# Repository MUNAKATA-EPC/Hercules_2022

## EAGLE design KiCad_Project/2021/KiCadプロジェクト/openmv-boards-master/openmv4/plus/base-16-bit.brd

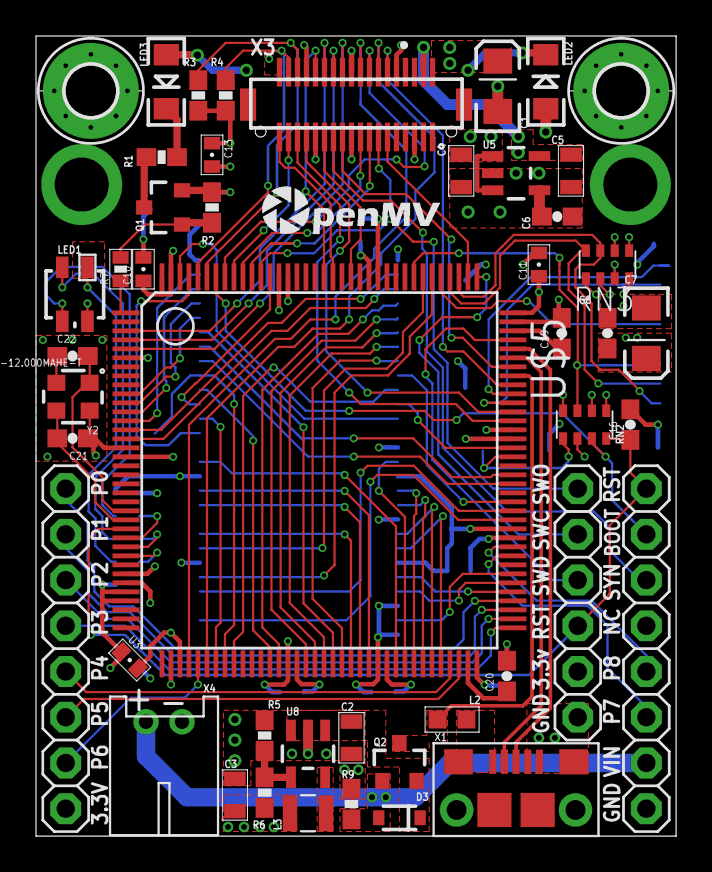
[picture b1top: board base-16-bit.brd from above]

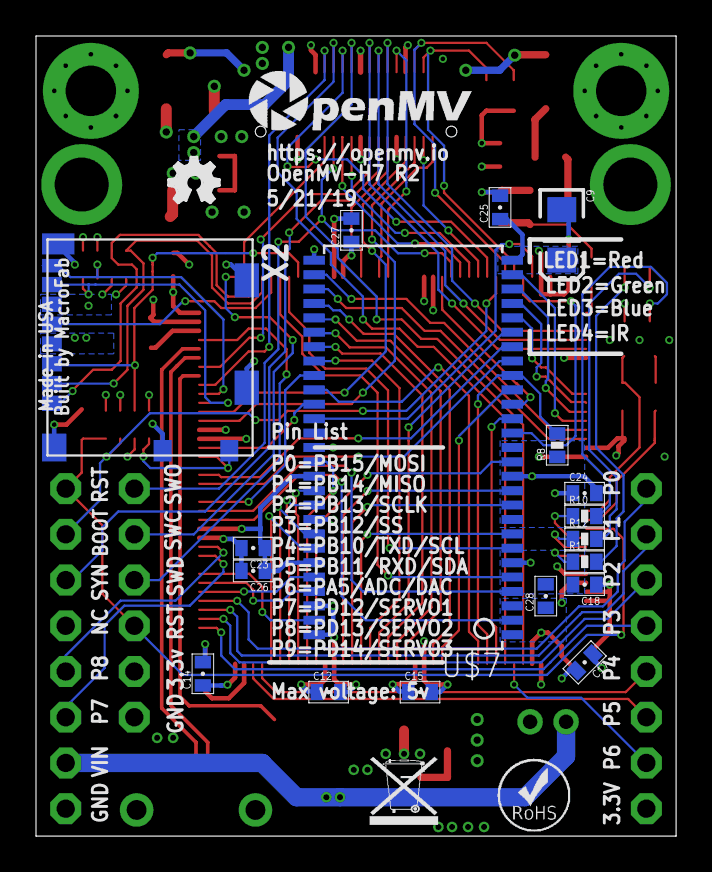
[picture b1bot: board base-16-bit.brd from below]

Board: 4 copper layers, 35.6 x 44.5 mm, 72 parts (22 on the bottom side), 108 nets.

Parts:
C1, C7: 47uF; EIA3216
C2, C3: 22uF; 0805
C4, C5: 10uF; 0805
C6, C8: 0.1uF; 0603-CAP
C9: 100uF; EIA3216
C10, C11, C12, C13, C14, C15, C18, C23, C24, C25, C26, C27, C28: 0.1uF; 0402-CAP
C16: 1uF; 0603-CAP
C17: 1uF; 0402-CAP
C19, C20: 2.2uF; 0603-CAP
C21, C22: 12pF; 0603-CAP
D3: SDM2U20SD3-7; SOD-323
H1, H2: MOUNT-PAD-ROUND2.8; 2,8-PAD
JP1, JP2: 1X08
JP3: 1X06
L2: MPZ1608S181ATAH0; 0603
L3: 4.7uH/1.4A; 1007
LED1: LED-TRICOLOR; LED-TRICOLOR-SMD
LED2, LED3: VSMY12850; LED-1206
LOGO1: OSHW_LOGO_FILLX0100-NT; OSHW_FILLX100_NOTEXT
M1, M2: 9774030243R; 9774030151R
Q1: BSS138; SOT23-3
Q2: Si2301BDS; SOT23-3
R1: 10R; 0603-RES
R2, R9: 10K; 0603-RES
R3, R4: 4.7K; 0603-RES
R5: 100K; 0603-RES
R6: 453K; 0603-RES
R7, R10, R11, R12: 220R; 0402-RES
R8: 10K; 0402-RES
RN2: 10K; EXBV8V
RN3: 220R; EXBV8V
U3: BEAD; 0402-CAP
U5: TPS731XX; SOT23-5
U8: PAM2305AABADJ; TSOT25
U$1: WEEE
U$2: ROHS
U$3: OMV-LOGO
U$4: OMV-LOGO-SMALL
U$5: STM32H743ZIT6; LQFP144@1
U$7: IS42S16160G; TSOPII-54
X1: MF-CON-MICROUSB-RIGHT; MICROUSB-RIGHT
X2: USD-1040310811; 1040310811
X3: DF12-36-DS
X4: S2B-PH-K-S(LF)(SN); JST-PH-2-THM-RA
Y2: 7S-12.000MAHE-T; CRYSTAL-2.5X2.0

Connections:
BOOT0: JP2.2, RN2.3, U$5.138
DAC: JP1.7, U$5.41
DCMI_CLK: U$5.100, X3.12
DCMI_D0: U$5.96, X3.31
DCMI_D1: U$5.97, X3.29
DCMI_D2: U$5.125, X3.35
DCMI_D3: U$5.126, X3.28
DCMI_D4: U$5.3, X3.26
DCMI_D5: U$5.136, X3.33
DCMI_D6: U$5.4, X3.24
DCMI_D7: U$5.5, X3.22
DCMI_FSIN: JP2.3, X3.23
DCMI_HSYNC: U$5.40, X3.18
DCMI_PCLK: U$5.42, X3.14
DCMI_PWDN: U$5.123, X3.25
DCMI_RST: U$5.102, X3.21
DCMI_VSYNC: U$5.137, X3.16
DRAM_A0: U$5.10, U$7.23
DRAM_A1: U$5.11, U$7.24
DRAM_A2: U$5.12, U$7.25
DRAM_A3: U$5.13, U$7.26
DRAM_A4: U$5.14, U$7.29
DRAM_A5: U$5.15, U$7.30
DRAM_A6: U$5.50, U$7.31
DRAM_A7: U$5.53, U$7.32
DRAM_A8: U$5.54, U$7.33
DRAM_A9: U$5.55, U$7.34
DRAM_A10: U$5.56, U$7.22
DRAM_A11: U$5.57, U$7.35
DRAM_A12: U$5.87, U$7.36
DRAM_BA0: U$5.89, U$7.20
DRAM_BA1: U$5.90, U$7.21
DRAM_CAS: U$5.132, U$7.17
DRAM_CLK: U$5.93, U$7.38
DRAM_CLKE: U$5.45, U$7.37
DRAM_CS: R8.2, U$5.44, U$7.19
DRAM_D0: U$5.85, U$7.2
DRAM_D1: U$5.86, U$7.4
DRAM_D2: U$5.114, U$7.5
DRAM_D3: U$5.115, U$7.7
DRAM_D4: U$5.58, U$7.8
DRAM_D5: U$5.59, U$7.10
DRAM_D6: U$5.60, U$7.11
DRAM_D7: U$5.63, U$7.13
DRAM_D8: U$5.64, U$7.42
DRAM_D9: U$5.65, U$7.44
DRAM_D10: U$5.66, U$7.45
DRAM_D11: U$5.67, U$7.47
DRAM_D12: U$5.68, U$7.48
DRAM_D13: U$5.77, U$7.50
DRAM_D14: U$5.78, U$7.51
DRAM_D15: U$5.79, U$7.53
DRAM_DQMH: U$5.142, U$7.39
DRAM_DQML: U$5.141, U$7.15
DRAM_RAS: U$5.49, U$7.18
DRAM_WE: U$5.43, U$7.16
FS_DM: U$5.103, X1.2
FS_DP: U$5.104, X1.3
GND: C1.C, C2.1, C3.1, C4.1, C5.1, C6.2, C7.C, C8.2, C9.C, C10.2, C11.2, C12.2, C13.2, C14.2, C15.2, C16.2, C17.2, C18.2, C19.2, C20.2, C21.1, C22.1, C23.2, C24.2, C25.2, C26.2, C27.2, C28.2, JP2.8, JP3.6, Q1.2, R2.1, R5.1, R9.1, RN2.6, U5.2, U8.2, U$5.16, U$5.31, U$5.38, U$5.51, U$5.61, U$5.83, U$5.94, U$5.107, U$5.120, U$5.130, U$7.6, U$7.12, U$7.28, U$7.41, U$7.46, U$7.52, U$7.54, X1.5, X2.CD$2, X2.G$1, X2.G$2, X2.G$3, X2.G$4, X2.P$6, X3.5, X3.19, X3.27, X4.2, Y2.2, Y2.4
I2C1_SCL: R3.2, U$5.139, X3.32
I2C1_SDA: R4.2, U$5.140, X3.34
I2C2_SCL: JP1.5, U$5.69
I2C2_SDA: JP1.6, U$5.70
LED_B: R11.1, U$5.28
LED_G: R12.1, U$5.27
LED_IR: R7.1, U$5.1
LED_R: R10.1, U$5.26
unnamed: Q1.1, R2.2, R7.2
unnamed: LED1.B, R11.2
unnamed: L2.1, X1.1
unnamed: LED1.R, R10.2
unnamed: LED1.G, R12.2
unnamed: LED3.C, R1.2
unnamed: C6.1, U5.4
unnamed: R5.2, R6.1, U8.4
unnamed: Q1.3, R1.1
unnamed: LED2.C, LED3.A
unnamed: C21.2, U$5.24, Y2.3
unnamed: C22.2, U$5.23, Y2.1
unnamed: C17.1, C18.1, U3.1, U$5.32, U$5.33
NRST: C16.1, JP2.1, JP3.4, RN2.4, U$5.25
RAW: C2.2, D3.1, Q2.2, U8.1, U8.3
SDIO_CLK: U$5.113, X2.P$5
SDIO_CMD: RN2.7, U$5.116, X2.P$3
SDIO_D0: RN3.8, U$5.98, X2.P$7
SDIO_D1: RN3.7, U$5.99, X2.P$8
SDIO_D2: RN3.3, U$5.111, X2.P$1
SDIO_D3: RN3.4, U$5.112, X2.P$2
SD_CD: RN2.1, U$5.92, X2.CD$1
SPI2_MISO: JP1.2, U$5.75
SPI2_MOSI: JP1.1, U$5.76
SPI2_NSS: JP1.4, U$5.73
SPI2_SCLK: JP1.3, U$5.74
SPI3_MISO: U$5.134, X3.15
SPI3_MOSI: U$5.135, X3.17
SPI3_SCLK/TRACESWO: JP3.1, U$5.133, X3.13
SPI3_SSEL: U$5.110, X3.11
SW: L3.1, U8.5
SWCLK: JP3.2, U$5.109
SWDIO: JP3.3, U$5.105
TIM4_CH1: JP2.6, U$5.81
TIM4_CH2: JP2.5, U$5.82
VBUS: L2.2, Q2.3, U$5.101
VCAP1: C19.1, U$5.106
VCAP2: C20.1, U$5.71
VCC: C1.A, C3.2, C4.2, C7.A, C8.1, C9.A, C10.1, C11.1, C12.1, C13.1, C14.1, C15.1, C23.1, C24.1, C25.1, C26.1, C27.1, C28.1, JP1.8, JP3.5, L3.2, LED1.A, LED2.A, R3.1, R4.1, R6.2, R8.1, RN2.2, RN2.5, RN2.8, RN3.1, RN3.2, RN3.5, RN3.6, U3.2, U5.1, U5.3, U$5.6, U$5.17, U$5.30, U$5.39, U$5.52, U$5.62, U$5.72, U$5.84, U$5.95, U$5.108, U$5.121, U$5.131, U$5.143, U$5.144, U$7.1, U$7.3, U$7.9, U$7.14, U$7.27, U$7.43, U$7.49, X2.P$4, X3.2, X3.10, X3.20, X3.30, X3.36
VDDA: C5.2, U5.5, X3.4
VIN: D3.2, JP2.7, Q2.1, R9.2, X4.1

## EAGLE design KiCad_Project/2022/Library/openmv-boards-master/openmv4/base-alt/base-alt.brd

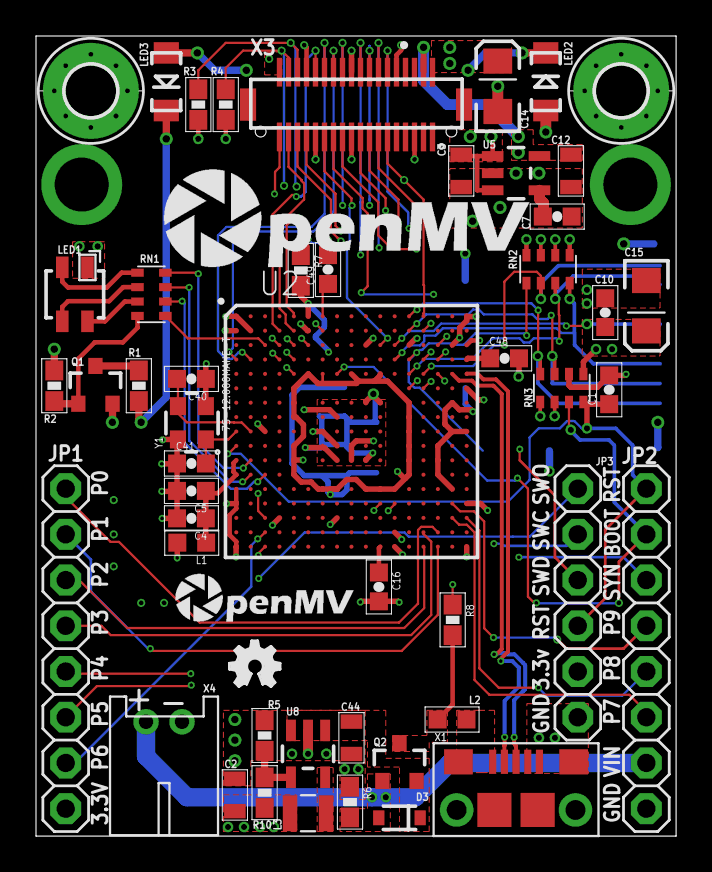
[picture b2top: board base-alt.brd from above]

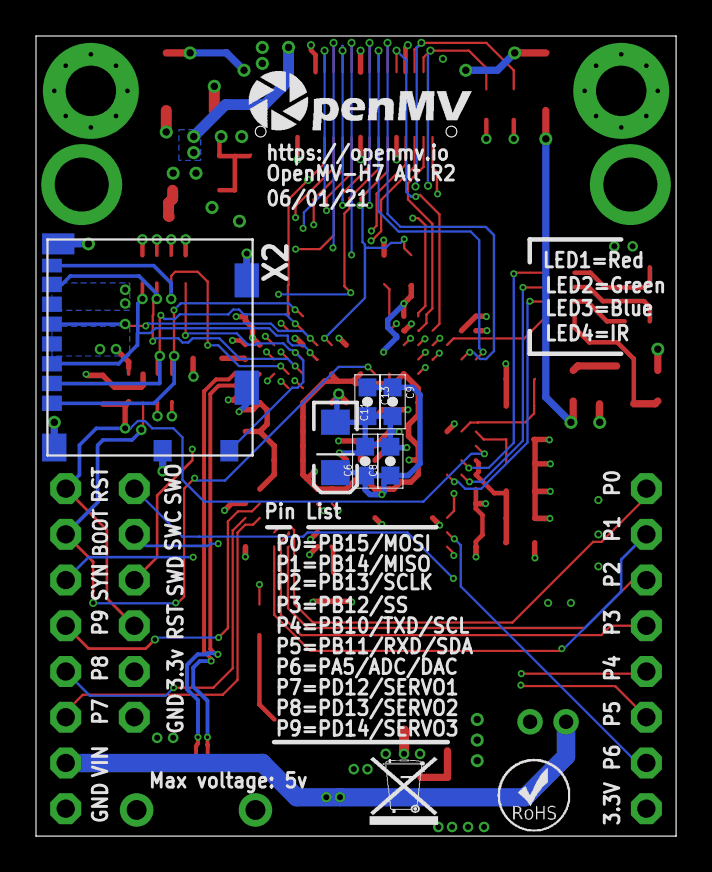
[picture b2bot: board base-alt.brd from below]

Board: 4 copper layers, 35.6 x 44.5 mm, 63 parts (9 on the bottom side), 72 nets.

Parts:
C1, C4: 1uF; 0603-CAP
C2, C44: 22uF; 0805
C3, C12: 10uF; 0805
C5, C6, C7, C8, C9, C10, C13: 0.1uF; 0603-CAP
C11, C14, C15: 47uF; EIA3216
C16, C48, C49: 2.2uF; 0603-CAP
C40, C41: 12pF; 0603-CAP
D3: SDM2U20SD3-7; SOD-323
H1, H2: MOUNT-PAD-ROUND2.8; 2,8-PAD
JP1, JP2: 1X08
JP3: 1X06
L1, L2: MPZ1608S181ATAH0; 0603
L3: 4.7uH/1.4A; 1007
LED1: LED-TRICOLOR; LED-TRICOLOR-SMD-MF
LED2, LED3: VSMY12850; LED-1206
LOGO1: OSHW_LOGO_FILLX0100-NT; OSHW_FILLX100_NOTEXT
M1, M2: 9774030243R; 9774030151R
Q1: BSS138; SOT23-3
Q2: Si2301BDS; SOT23-3
R1: 10R; 0603-RES
R2, R7: 10K; 0603-RES
R3, R4: 4.7K; 0603-RES
R5, R6: 100K; 0603-RES
R8: 560R; 0603-RES
R10: 453K; 0603-RES
RN1: 220R; EXBV8V
RN2, RN3: 10K; EXBV8V
U2: STM32H743XIH6; TFBGA240+25
U5: TPS731XX; SOT23-5
U8: PAM2305AABADJ; TSOT25
U$1: WEEE
U$2: ROHS
U$3: OMV-LOGO
U$4: OMV-LOGO-SMALL
U$6: OMV-LOGO-BIG
X1: MF-CON-MICROUSB-RIGHT; MICROUSB-RIGHT
X2: USD-1040310811; 1040310811
X3: DF12-36-DS
X4: S2B-PH-K-S(LF)(SN); JST-PH-2-THM-RA
Y1: 7S-12.000MAHE-T; CRYSTAL-2.5X2.0

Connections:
BOOT0: JP2.2, RN3.3, U2.E8
DAC: JP1.7, U2.T3
DCMI_CLK: U2.E15, X3.12
DCMI_D0: U2.F14, X3.31
DCMI_D1: U2.F13, X3.29
DCMI_D2: U2.C4, X3.35
DCMI_D3: U2.B4, X3.28
DCMI_D4: U2.D2, X3.26
DCMI_D5: U2.B5, X3.33
DCMI_D6: U2.D1, X3.24
DCMI_D7: U2.E5, X3.22
DCMI_FSIN: JP2.3, X3.23
DCMI_HSYNC: U2.U3, X3.18
DCMI_PCLK: U2.R3, X3.14
DCMI_PWDN: R7.1, U2.C11, X3.25
DCMI_RST: U2.D14, X3.21
DCMI_VSYNC: U2.C5, X3.16
FS_D_N: U2.E17, X1.2
FS_D_P: U2.E16, X1.3
GND: C1.2, C2.1, C3.1, C4.2, C5.2, C6.2, C7.2, C8.2, C9.2, C10.2, C11.C, C12.1, C13.2, C14.C, C15.C, C16.2, C40.1, C41.1, C44.1, C48.2, C49.2, JP2.8, JP3.6, Q1.2, R2.1, R5.1, R6.1, RN3.6, U2.A1, U2.A17, U2.B2, U2.B6, U2.C10, U2.C13, U2.C16, U2.G7, U2.G8, U2.G9, U2.G10, U2.G11, U2.G16, U2.H7, U2.H8, U2.H9, U2.H10, U2.H11, U2.J3, U2.J7, U2.J8, U2.J9, U2.J10, U2.J11, U2.J16, U2.J17, U2.K7, U2.K8, U2.K9, U2.K10, U2.K11, U2.K15, U2.L7, U2.L8, U2.L9, U2.L10, U2.L11, U2.L15, U2.M15, U2.N1, U2.N16, U2.P1, U2.R4, U2.R8, U2.T12, U2.U1, U2.U17, U5.2, U8.2, X1.5, X2.CD$2, X2.G$1, X2.G$2, X2.G$3, X2.G$4, X2.P$6, X3.5, X3.19, X3.27, X4.2, Y1.2, Y1.4
I2C1_SCL: R3.2, U2.D5, X3.32
I2C1_SDA: R4.2, U2.D4, X3.34
I2C2_SCL: JP1.5, U2.P11
I2C2_SDA: JP1.6, U2.P12
LED_B: RN1.6, U2.M3
LED_G: RN1.7, U2.M2
LED_IR: RN1.5, U2.C3
LED_R: RN1.8, U2.L2
unnamed: C40.2, U2.J2, Y1.3
unnamed: C41.2, U2.J1, Y1.1
unnamed: Q1.1, R2.2, RN1.4
unnamed: LED1.B, RN1.3
unnamed: L2.1, X1.1
unnamed: LED1.R, RN1.1
unnamed: LED1.G, RN1.2
unnamed: LED3.C, R1.2
unnamed: C7.1, U5.4
unnamed: R5.2, R10.1, U8.4
unnamed: Q1.3, R1.1
unnamed: LED2.C, LED3.A
unnamed: R8.1, U2.D15
unnamed: C4.1, C5.1, L1.1, U2.L1, U2.M1
unnamed: C49.1, U2.A7
unnamed: C48.1, U2.D17
unnamed: C16.1, U2.U11
NRST: C1.1, JP2.1, JP3.4, RN3.4, U2.K1
RAW: C44.2, D3.1, Q2.2, U8.1, U8.3
SDIO_CLK: U2.C12, X2.P$5
SDIO_CMD: RN2.8, U2.D12, X2.P$3
SDIO_D0: RN2.7, U2.E13, X2.P$7
SDIO_D1: RN2.6, U2.E14, X2.P$8
SDIO_D2: RN3.8, U2.A13, X2.P$1
SDIO_D3: RN3.7, U2.B13, X2.P$2
SD_CD: RN2.5, U2.D13, X2.CD$1
SPI2_MISO: JP1.2, U2.U15
SPI2_MOSI: JP1.1, U2.T15
SPI2_NSS: JP1.4, U2.T14
SPI2_SCLK: JP1.3, U2.U14
SPI3_MISO: U2.B7, X3.15
SPI3_MOSI: U2.A5, X3.17
SPI3_SCLK/TRACESWO: JP3.1, U2.C6, X3.13
SPI3_SSEL: U2.A14, X3.11
SW: L3.1, U8.5
SWCLK: JP3.2, U2.B14
SWDIO: JP3.3, U2.C15
TIM4_CH1: JP2.6, U2.R16
TIM4_CH2: JP2.5, U2.R17
TIM4_CH3: JP2.4, U2.P16
VBUS: L2.2, Q2.3, R8.2
VCC: C2.2, C3.2, C6.1, C8.1, C9.1, C10.1, C11.A, C13.1, C14.A, C15.A, JP1.8, JP3.5, L1.2, L3.2, LED1.A, LED2.A, R3.1, R4.1, R7.2, R10.2, RN2.1, RN2.2, RN2.3, RN2.4, RN3.1, RN3.2, RN3.5, U2.A6, U2.B1, U2.C17, U2.E6, U2.E7, U2.E9, U2.E11, U2.F5, U2.F17, U2.G5, U2.G13, U2.H5, U2.H13, U2.J13, U2.K5, U2.K13, U2.L5, U2.L13, U2.M5, U2.M13, U2.N7, U2.N8, U2.N10, U2.N11, U2.N12, U2.P17, U2.U12, U5.1, U5.3, X2.P$4, X3.2, X3.10, X3.20, X3.30, X3.36
VDDA: C12.2, U5.5, X3.4
VIN: D3.2, JP2.7, Q2.1, R6.2, X4.1

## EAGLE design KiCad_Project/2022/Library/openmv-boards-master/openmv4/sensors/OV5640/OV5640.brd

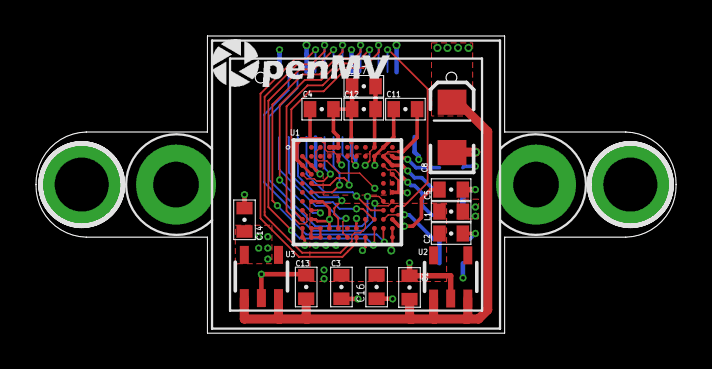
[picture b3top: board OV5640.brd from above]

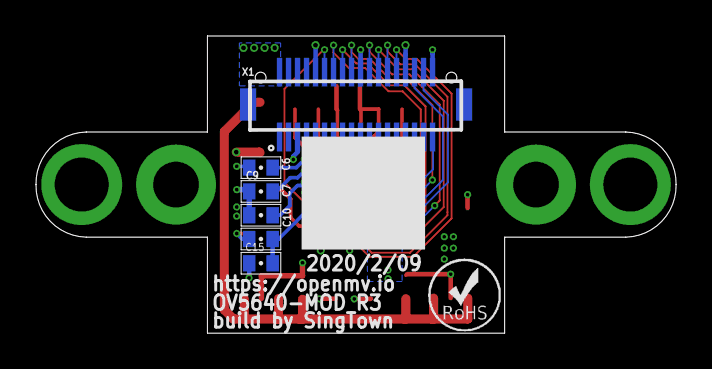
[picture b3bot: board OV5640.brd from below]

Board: 4 copper layers, 35.6 x 16.5 mm, 25 parts (7 on the bottom side), 24 nets.

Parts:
C1, C2, C3, C4, C13, C14: 1uF; 0402-CAP
C5, C6, C7, C9, C10, C11, C12: 0.1uF; 0402-CAP
C8: 47uF; EIA3216
C15, C16, C17: 10uF; 0402-CAP
L1: MPZ1608S181ATAH0; 0402-CAP
LM1: LENSMOUNT20MM; LENSMOUNT-20MM
U1: OV5640-A71A; BGA71C50P11X11_598X584X81
U2: ME6211C28M5G; SOT23-5
U3: ME6211C15M5G; SOT23-5
U$2: ROHS
U$6: OMV-LOGO-SMALL
X1: DF12-36-DP

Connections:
1V5: C4.2, C5.2, C12.2, C14.2, C17.2, U1.A9, U1.B5, U1.C1, U1.D2, U1.I11, U1.J1, U1.J7, U1.K1, U3.5
2V8: C2.2, C3.1, C16.2, L1.1, U1.J2, U1.J3, U1.K2, U1.K3, U2.5
AVDD: C9.2, C10.2, C11.2, C15.2, L1.2, U1.A3, U1.B10, U1.C11, U1.I10
DCMI_CLK: U1.H11, X1.12
DCMI_D0: U1.J5, X1.31
DCMI_D1: U1.H10, X1.29
DCMI_D2: U1.K6, X1.35
DCMI_D3: U1.K7, X1.28
DCMI_D4: U1.I8, X1.26
DCMI_D5: U1.I9, X1.33
DCMI_D6: U1.J9, X1.24
DCMI_D7: U1.J10, X1.22
DCMI_FSIN: U1.F2, X1.23
DCMI_HSYNC: U1.H2, X1.18
DCMI_PCLK: U1.I1, X1.14
DCMI_PWDN: U1.D1, X1.25
DCMI_RST: U1.E2, X1.21
DCMI_VSYNC: U1.H1, X1.16
GND: C1.1, C2.1, C3.2, C4.1, C5.1, C6.1, C7.1, C8.C, C9.1, C10.1, C11.1, C12.1, C13.1, C14.1, C15.1, C16.1, C17.1, U1.A4, U1.A5, U1.A10, U1.B1, U1.B9, U1.C2, U1.D11, U1.F11, U1.G2, U1.I2, U1.J4, U1.J11, U1.K8, U1.K11, U2.2, U3.2, X1.5, X1.19, X1.27
I2C1_SCL: U1.G10, X1.32
I2C1_SDA: U1.G11, X1.34
VCC: C1.2, C8.A, C13.2, U2.1, U2.3, U3.1, U3.3, X1.2, X1.10, X1.20, X1.30, X1.36
VH: C7.2, U1.C10
VN: C6.2, U1.B11

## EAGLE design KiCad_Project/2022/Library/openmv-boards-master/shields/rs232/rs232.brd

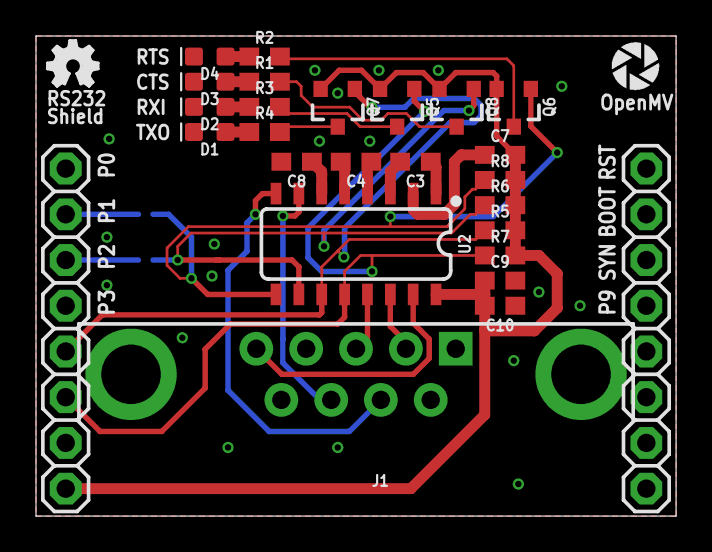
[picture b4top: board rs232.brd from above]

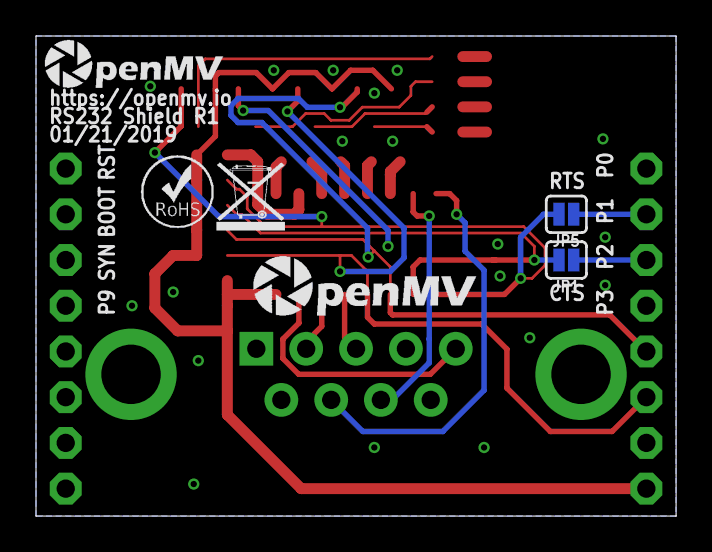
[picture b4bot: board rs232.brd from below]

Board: 2 copper layers, 35.6 x 26.7 mm, 33 parts (6 on the bottom side), 26 nets.

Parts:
C3, C4, C7, C8, C9: 1.0uF; 0603
C10: 0.1uF; 0603
D1: RED; LED-0603
D2: BLUE; LED-0603
D3: GREEN; LED-0603
D4: Yellow; LED-0603
J1: DB9
JP1, JP5: JUMPER-SMT_2_NO_SILK; SMT-JUMPER_2_NO_SILK
Q5, Q6, Q7, Q8: 2.5A/30V/105mΩ; SOT23-3
R1, R2, R3, R4: 1k; 0603
R5, R6, R7, R8: 10k; 0603
U2: MAX3232; SO16
U3: OPENMV3
U$3: OMV-LOGO
U$5: ROHS
U$6: WEEE
U$9: OPENMV-LOGO
U$10: OMV-LOGO-SMALL
U$11: OSHW_FILLX100_NOTEXT

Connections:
3V3: C7.2, C9.1, C10.2, Q5.2, Q6.2, Q7.2, Q8.2, R5.2, R6.2, R7.2, R8.2, U2.16, U3.18
CTS_O: JP1.2, Q8.1, R6.1, U2.10
GND: C8.2, C9.2, C10.1, D1.C, D2.C, D3.C, D4.C, J1.5, U2.15, U3.28
INT_CTS_O: JP1.1, U3.13
INT_RTS_I: JP5.1, U3.12
unnamed: C4.2, U2.5
unnamed: C4.1, U2.4
unnamed: C3.2, U2.3
unnamed: C3.1, U2.1
unnamed: C8.1, U2.6
unnamed: Q7.3, R4.2
unnamed: Q5.3, R3.2
unnamed: Q6.3, R2.2
unnamed: C7.1, U2.2
unnamed: Q8.3, R1.2
unnamed: D4.A, R2.1
unnamed: D3.A, R1.1
unnamed: D2.A, R3.1
unnamed: D1.A, R4.1
RS232_CTS_O: J1.8, U2.7
RS232_RTS_I: J1.7, U2.8
RS232_RXI: J1.3, U2.13
RS232_TXO: J1.2, U2.14
RTS_I: JP5.2, Q6.1, R8.1, U2.9
RXI: Q5.1, R7.1, U2.12, U3.16
TXO: Q7.1, R5.1, U2.11, U3.15

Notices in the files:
parts and their libraries:
SparkFun-Connectors: Licensing: Creative Commons ShareAlike 4.0 International - https://creativecommons.org/licenses/by-sa/4.0
